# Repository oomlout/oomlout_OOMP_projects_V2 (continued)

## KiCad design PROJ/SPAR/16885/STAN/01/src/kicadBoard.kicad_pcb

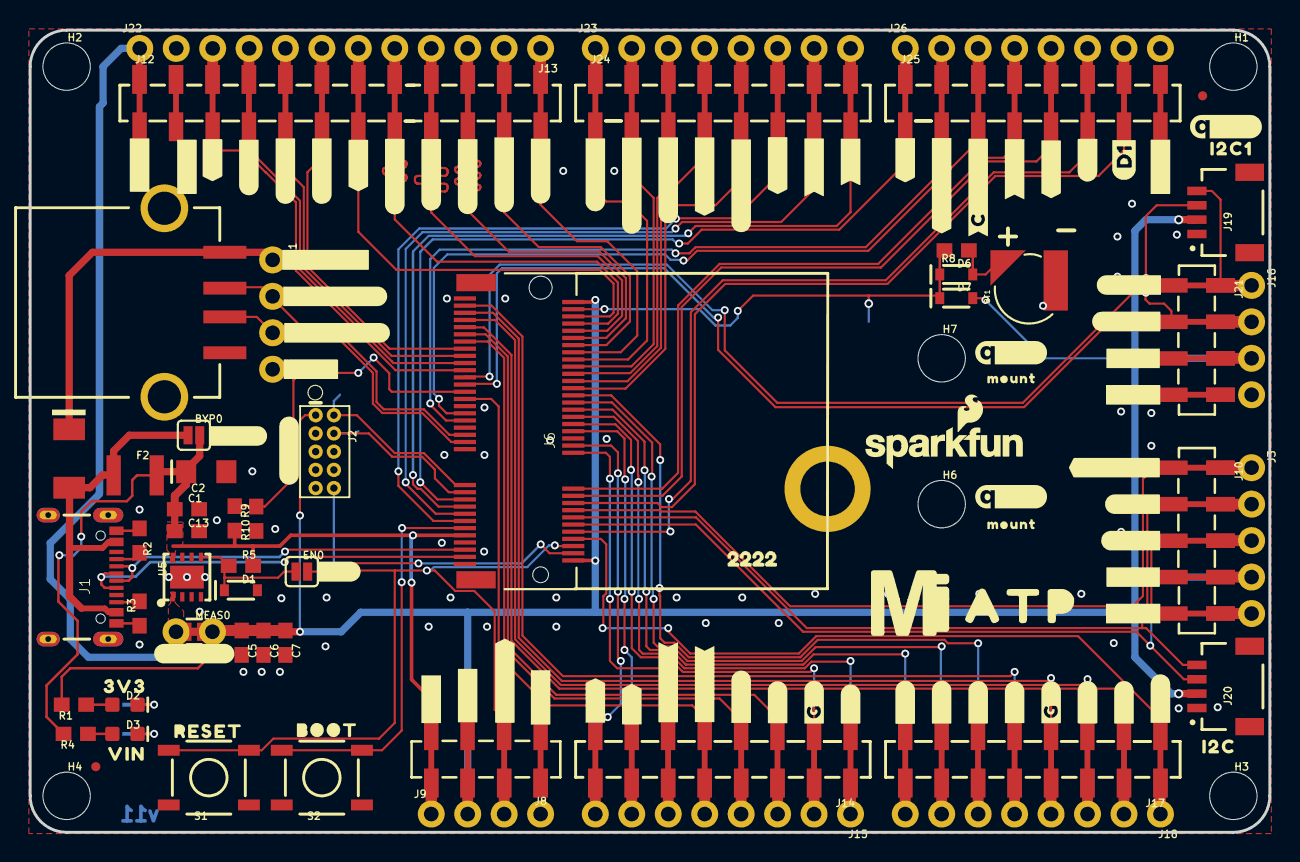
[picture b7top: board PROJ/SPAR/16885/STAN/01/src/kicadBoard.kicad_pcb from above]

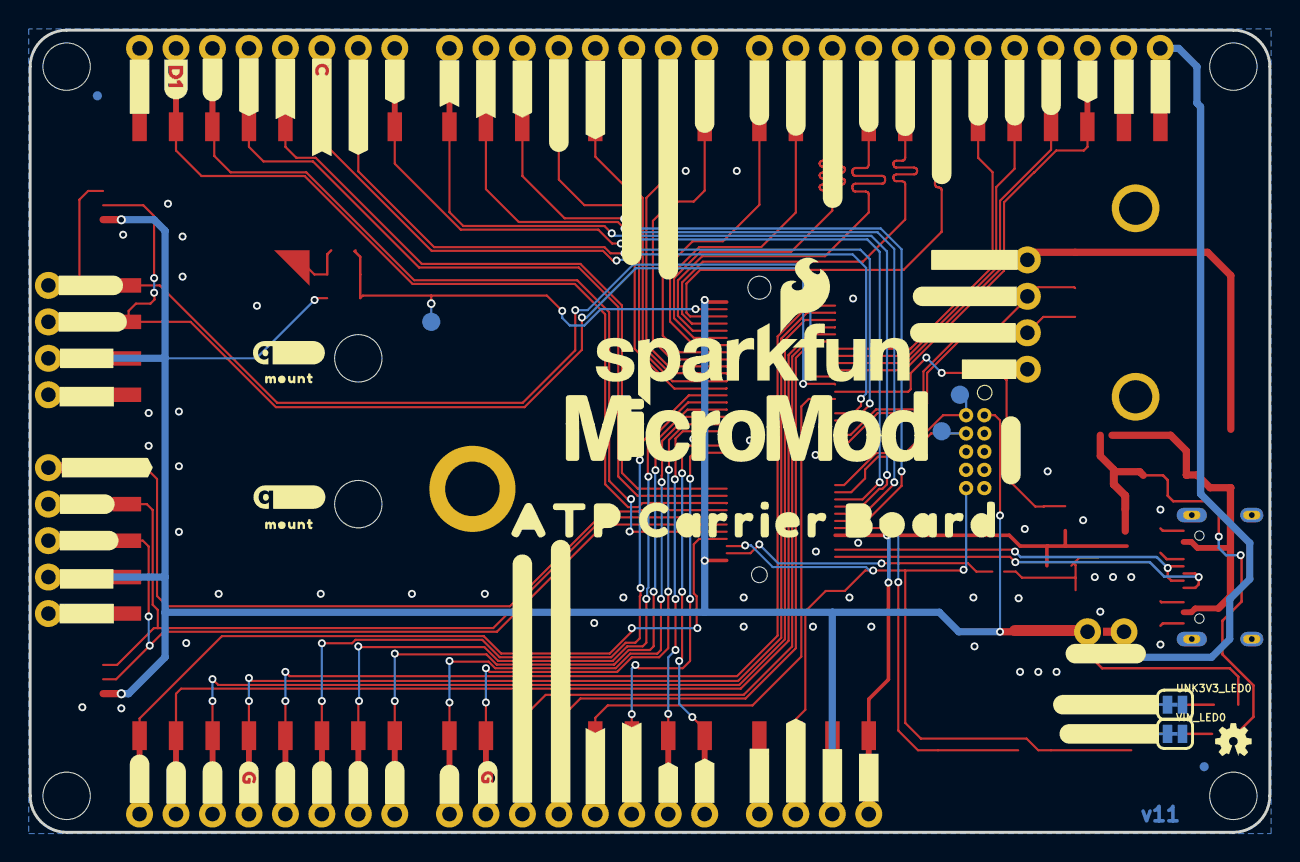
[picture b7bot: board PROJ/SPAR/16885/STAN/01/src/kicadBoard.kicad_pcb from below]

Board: 2 copper layers, 86.4 x 55.9 mm, 222 parts (80 on the bottom side), 71 nets.

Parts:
BT1: ML414H; ML414H_IV01E
BYP0: JUMPER-SMT_2_NO_SILK; SMT-JUMPER_2_NO_SILK
C1, C6: 0.1uF; 0603
C2: 10uF; EIA3216
C5: 1.0uF; 0603
C7, C13: 0.22uF; 0603
D1: 3.3V; SOD-323
D2, D3: RED; LED-0603
D4: 1A/15V/220mV; DO-214BA
D6: 3A/10V/280mV; SOD-323
D7: 1A/23V/620mV; SOD-323
EN0: JUMPER-SMT_2_NO_SILK; SMT-JUMPER_2_NO_SILK
F2: 6V/2A; 1210
FD1, FD2, FD3, FD4: FIDUCIALUFIDUCIAL; FIDUCIAL-MICRO
FRAME1: FRAME-LEDGER; CREATIVE_COMMONS
H1, H2, H3, H4, H6, H7: STAND-OFF
H5: STAND-OFF-REFLOW2.5MM_TALL; STAND-OFF-REFLOW-M2.5
J1: USB-C-16P-2LAYER-PADS
J2: JTAG; 2X5-PTH-1.27MM
J3: 1X05_NO_SILK
J4: USB_A_SMT_FEMALE; USB-A-S-SILK-FEMALE
J6: MICROMOD-2222-C; M.2-CONNECTOR-E
J8, J21: 1X04_SMD_STRAIGHT_COMBO; 1X04_SMD_VERTICAL_COMBO
J9, J11, J16, J22: 1X04_NO_SILK
J10: 1X05_SMD_VERTICAL_COMBO
J12: 1X12_SMD_COMBINED
J13, J15, J18, J23, J26: 1X08_NO_SILK
J14, J17, J24, J25: 1X08_SMD_COMBINED
J19, J20: QWIIC_RIGHT_ANGLE; JST04_1MM_RA
LOGO1: SFE_LOGO_NAME_FLAME.1_INCH; SFE_LOGO_NAME_FLAME_.1
LOGO2: QWIIC_LOGO_5MM; QWIIC_5MM
LOGO3: OSHW-LOGOMINI; OSHW-LOGO-MINI
LOGO4: SFE_LOGO_NAME_FLAME.2_INCH; SFE_LOGO_NAME_FLAME_.2
LOGO5, LOGO6, LOGO7, LOGO8: QWIIC_LOGO_3MM; QWIIC_5MM
MEAS0: COMBO-JUMPER_2_NC_TRACE
R1, R4, R8: 1k; 0603
R2, R3: 5.1k; 0603
R5: 100k; 0603
R9: 10k; 0603
R10: 20k; 0603
S1: Reset; TACTILE_SWITCH_SMD_5.2MM
S2: BOOT; TACTILE_SWITCH_SMD_5.2MM
TP1, TP2, TP3: TEST-POINT3X5; PAD.03X.05
U5: AP7361C-33; UDFN-8
U$1, U$123: #A0#10
U$2, U$124: #A1#10
U$3, U$27, U$46, U$47, U$58, U$89, U$100, U$101, U$102, U$103, U$104, U$105: #GND#0
U$4, U$120: #G0#2
U$5: #RESET10
U$6, U$98: #D0#0
U$7, U$119: #G1#2
U$8, U$118: #G2#2
U$9, U$117: #G3#3
U$10, U$116: #G4#4
U$11, U$115: #G5#5
U$12, U$114: #G6#6
U$13, U$113: #G7#7
U$14, U$112: #G8#8
U$15: #G9#9
U$16: #G10#10
U$17, U$111: #G11#10
U$18, U$121: #PWM0#10
U$19, U$122: #PWM1#10
U$20: ##CS1##5178039
U$21, U$110: ##I2C_INT##10
U$22: #CAN_RX#9
U$23, U$97: #CAN_TX#10
U$24: #CIPO#3
U$25: #COPI#2
U$26: #CTS#6
U$28: #SCK#2
U$29: #I2S_FS#5
U$30: #I2S_SDI#5
U$31: #I2S_SDO#5
U$32: #MCLK#4
U$33: #RTS#5
U$34: #RX#8
U$35: #TX#7
U$36: #DAT1#5178039
U$37, U$125: ##RESET##7
U$38, U$60, U$61, U$70, U$88, U$106, U$107, U$126: #3V3#1
U$39: #BYP#8
U$40, U$128: #HOST_D##9
U$41, U$129: #HOST_D##10
U$42, U$132: #MEAS#10
U$43: BOOT10
U$44, U$108: #SDA#4
U$45, U$127: #VIN#6
U$48: #EN#0
U$49, U$109: #SCL#5
U$50, U$146: #VHOST#0
U$51, U$131: #SWD#10
U$52: #I2S_CLK#5
U$53: #DAT2#5178039
U$54: #CIPO1#5178039
U$55: 22229
U$56: ##CIPO1##DAT0#5178038
U$57, U$75: #COPI1#2
U$59: ##CS##0
U$62: ATP0
U$63, U$76: #RX2#3
U$64, U$80: #TX2#2
U$65, U$78: #SCL1#3
U$66, U$79: #SDA1#3
U$67, U$77: #SCK1#2
U$68: VIN3
U$69: 3V34
U$71: I2C4
U$72: I2C14
U$73: ATP_CARRIER_BOARD1
U$81: ##CS##5178037
U$82: #DAT2#5
U$83: #DAT1#5
U$84: ##CS1##DAT3#5178037
U$85: #COPI#4
U$86: #SCK#4
U$87: #MCLK#6
U$90: #I2S_FS#7
U$91: #I2S_CLK#7
U$92: #RTS#7
U$93: #CTS#8
U$94: #TX#9
U$95: #RX#10
U$96: #CAN_RX#10
U$99, U$145: D10
U$133: #VIN_LED#10
U$134: #3V3_LED#10
U$135: #G9#ADC##CAM_HSYNC#9
U$136: #G10#ADC##CAM_VSYNC#10
U$137: #I2S_SDI#CAM_PCLK#7
U$138: #I2S_SDO#CAM_MCLK#7
U$139, U$141, U$142, U$143: MOUNT10
U$140: MICROMOD_MI_LOGO_1
U$144: MICROMOD_LOGO_1
U$147: #CIPO#5178038
UNK3V3_LED0: JUMPER-SMT_2_NC_TRACE_SILK; SMT-JUMPER_2_NC_TRACE_SILK
VIN_LED0: JUMPER-SMT_2_NC_TRACE_SILK; SMT-JUMPER_2_NC_TRACE_SILK

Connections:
3.3V: C5.1, C6.1, C7.1, D7.A, J2.1, J3.4, J6.2, J6.74, J8.3, J9.2, J10.4, J12.1, J16.3, J19.2, J20.2, J21.3, J22.1, MEAS0.2, MEAS0.4, R1.2
3.3V_EN: D1.C, EN0.1, R5.1, U5.5
A0: J6.34, J14.8, J15.8
A1: J6.38, J14.7, J15.7
CAN_RXI: J6.41, J25.2, J26.2
CAN_TXO: J6.43, J25.3, J26.3
CIPO: J6.61, J12.6, J13.7
CIPO1/DAT0: J6.64, J12.10, J13.3
COPI: J6.59, J12.5, J13.8
COPI1: J6.62, J12.11, J13.2
CTS1: J6.15, J23.7, J24.7
D0: J6.10, J25.6, J26.6
D1: J6.18, J25.7, J26.7
DAT1: J6.66, J12.9, J13.4
DAT2: J6.68, J12.8, J13.5
G0: J6.40, J14.2, J15.2
G1: J6.42, J14.1, J15.1
G2: J6.44, J17.8, J18.8
G3: J6.46, J17.7, J18.7
G4: J6.48, J17.6, J18.6
G5: J6.73, J17.5, J18.5
G6: J6.71, J17.4, J18.4
G7: J6.69, J17.3, J18.3
G8: J6.67, J17.2, J18.2
G9/ADC_N: J6.65, J14.3, J15.3
G10/ADC_P: J6.63, J14.4, J15.4
G11: J6.8, J17.1, J18.1
GND: BT1.-, C1.2, C2.-, C5.2, C6.2, C7.2, C13.2, D1.A, H5.1, J1.GND, J1.GND2, J2.3, J2.5, J2.9, J3.5, J4.GND, J4.SHLD1, J4.SHLD2, J6.1, J6.7, J6.33, J6.36, J6.39, J6.45, J6.75, J8.1, J9.4, J10.5, J11.4, J12.2, J16.4, J19.1, J20.1, J21.4, J22.2, J25.8, J26.8, R2.1, R3.1, R9.1, S1.1, S1.2, S2.1, S2.2, U5.4, U5.EP, UNK3V3_LED0.2, VIN_LED0.2
I2C_~INT: J3.1, J6.16, J10.1
I2S_CLK: J6.50, J23.5, J24.5
I2S_SDI: J6.54, J23.3, J24.3
I2S_SDO: J6.56, J23.2, J24.2
I2S_WS: J6.52, J23.4, J24.4
MCLK: J6.58, J23.1, J24.1
unnamed: D2.A, R1.1
unnamed: D3.A, R4.1
unnamed: D2.C, UNK3V3_LED0.1
unnamed: D3.C, VIN_LED0.1
unnamed: EN0.2, J6.4
unnamed: D4.C, J4.VBUS, J11.1
unnamed: J1.A5, R2.2
unnamed: J1.B5, R3.2
unnamed: BT1.+, D6.A, R8.1
OUT_MEAS: MEAS0.1, MEAS0.3, U5.1
PWM0: J6.32, J14.6, J15.6
PWM1: J6.47, J14.5, J15.5
RTC_3V: D6.C, D7.C, J6.72, R8.2, TP1.P$1
RTS1: J6.13, J23.6, J24.6
RX1: J6.19, J25.1, J26.1
RX2: J6.20, J25.5, J26.5
SCK: J6.57, J12.4, J22.4
SCK1: J6.60, J12.12, J13.1
SCL: J3.2, J6.14, J10.2, J20.4
SCL1: J6.53, J16.1, J19.4, J21.1
SDA: J3.3, J6.12, J10.3, J20.3
SDA1: J6.51, J16.2, J19.3, J21.2
SWDCK: J2.4, J6.21, TP3.P$1
SWDIO: J2.2, J6.23, TP2.P$1
TX1: J6.17, J23.8, J24.8
TX2: J6.22, J25.4, J26.4
USBHOST_N: J4.D-, J6.37, J11.2
USBHOST_P: J4.D+, J6.35, J11.3
USB_N: J1.A7, J1.B7, J6.5
USB_P: J1.A6, J1.B6, J6.3
VIN: BYP0.2, C1.1, C2.+, C13.1, F2.2, J6.9, J8.4, J9.1, R4.2, R5.2, R10.2, U5.8
VIN/3: J6.49, R9.2, R10.1
V_USB: BYP0.1, D4.A, F2.1, J1.VBUS1, J1.VBUS2
~BOOT: J6.11, S2.3, S2.4
~CS1/DAT3: J6.70, J12.7, J13.6
~CS: J6.55, J12.3, J22.3
~RESET: J2.10, J6.6, J8.2, J9.3, S1.3, S1.4

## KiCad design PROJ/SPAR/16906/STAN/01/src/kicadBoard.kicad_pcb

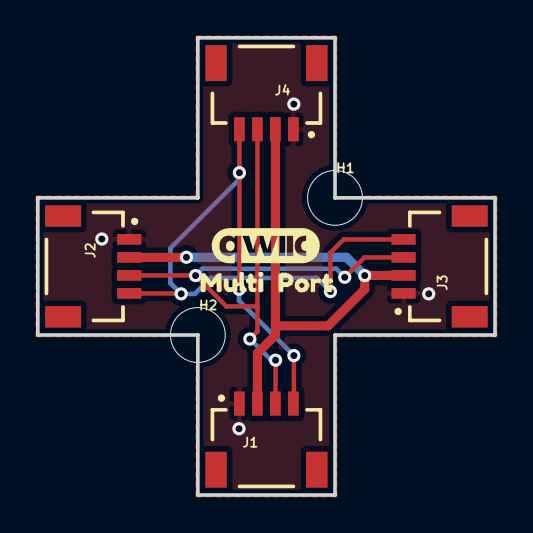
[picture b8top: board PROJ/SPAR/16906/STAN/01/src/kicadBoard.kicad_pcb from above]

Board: 2 copper layers, 25.4 x 25.4 mm, 14 parts (4 on the bottom side), 4 nets.

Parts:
FRAME1: FRAME-LETTER; CREATIVE_COMMONS
H1, H2: STAND-OFFTIGHT; STAND-OFF-TIGHT
J1, J2, J3, J4: QWIIC_RIGHT_ANGLE; JST04_1MM_RA
U$1, U$3: QWIIC_6MM
U$2: SPARKX-SMALL
U$4, U$7: MULTI1
U$5, U$8: PORT2

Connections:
3.3V: J1.2, J2.2, J3.2, J4.2
GND: J1.1, J2.1, J3.1, J4.1
SCL: J1.4, J2.4, J3.4, J4.4
SDA: J1.3, J2.3, J3.3, J4.3
